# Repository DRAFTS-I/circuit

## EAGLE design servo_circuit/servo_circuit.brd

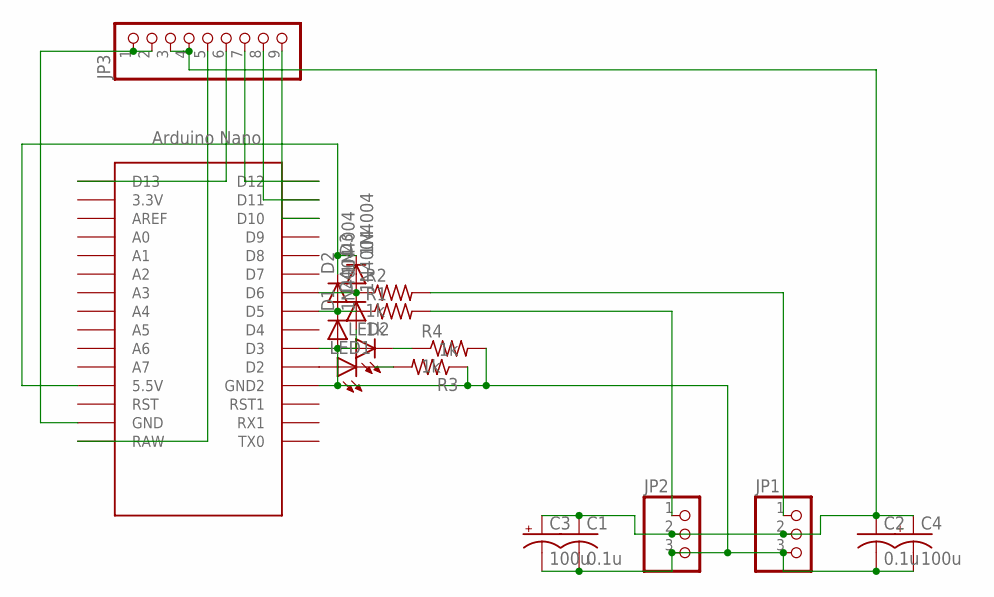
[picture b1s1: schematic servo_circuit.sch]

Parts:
C1, C2: 0.1u; C050-024X044
C3, C4: 100u; TT2D5
D1, D2, D3, D4: 1N4004; DO41-10
JP1, JP2: PINHD-1X3; 1X03
JP3: PINHD-1X9; 1X09
LED1, LED2: LED3MM
R1, R2, R3, R4: 1k; 0309V
U$1: NANO

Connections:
unnamed: LED1.A, U$1.D2
unnamed: JP3.1, JP3.2, U$1.GND
unnamed: C1.1, C2.1, C3.+, C4.+, JP1.2, JP2.2, JP3.3, JP3.4
unnamed: LED2.A, U$1.D3
unnamed: JP2.1, R1.2
unnamed: JP1.1, R2.2
unnamed: D1.C, D2.A, R1.1, U$1.D5
unnamed: D3.A, D4.C, R2.1, U$1.D6
unnamed: D2.C, D3.C, U$1.5V (5.5V)
unnamed: C1.2, C2.2, C3.-, C4.-, D1.A, D4.A, JP1.3, JP2.3, R3.1, R4.2, U$1.GND1 (GND2)
unnamed: LED2.K (C), R4.1
unnamed: JP3.5, U$1.RAW
unnamed: JP3.6, U$1.D13
unnamed: JP3.7, U$1.D12
unnamed: JP3.8, U$1.D11
unnamed: JP3.9, U$1.D10
unnamed: LED1.K (C), R3.2

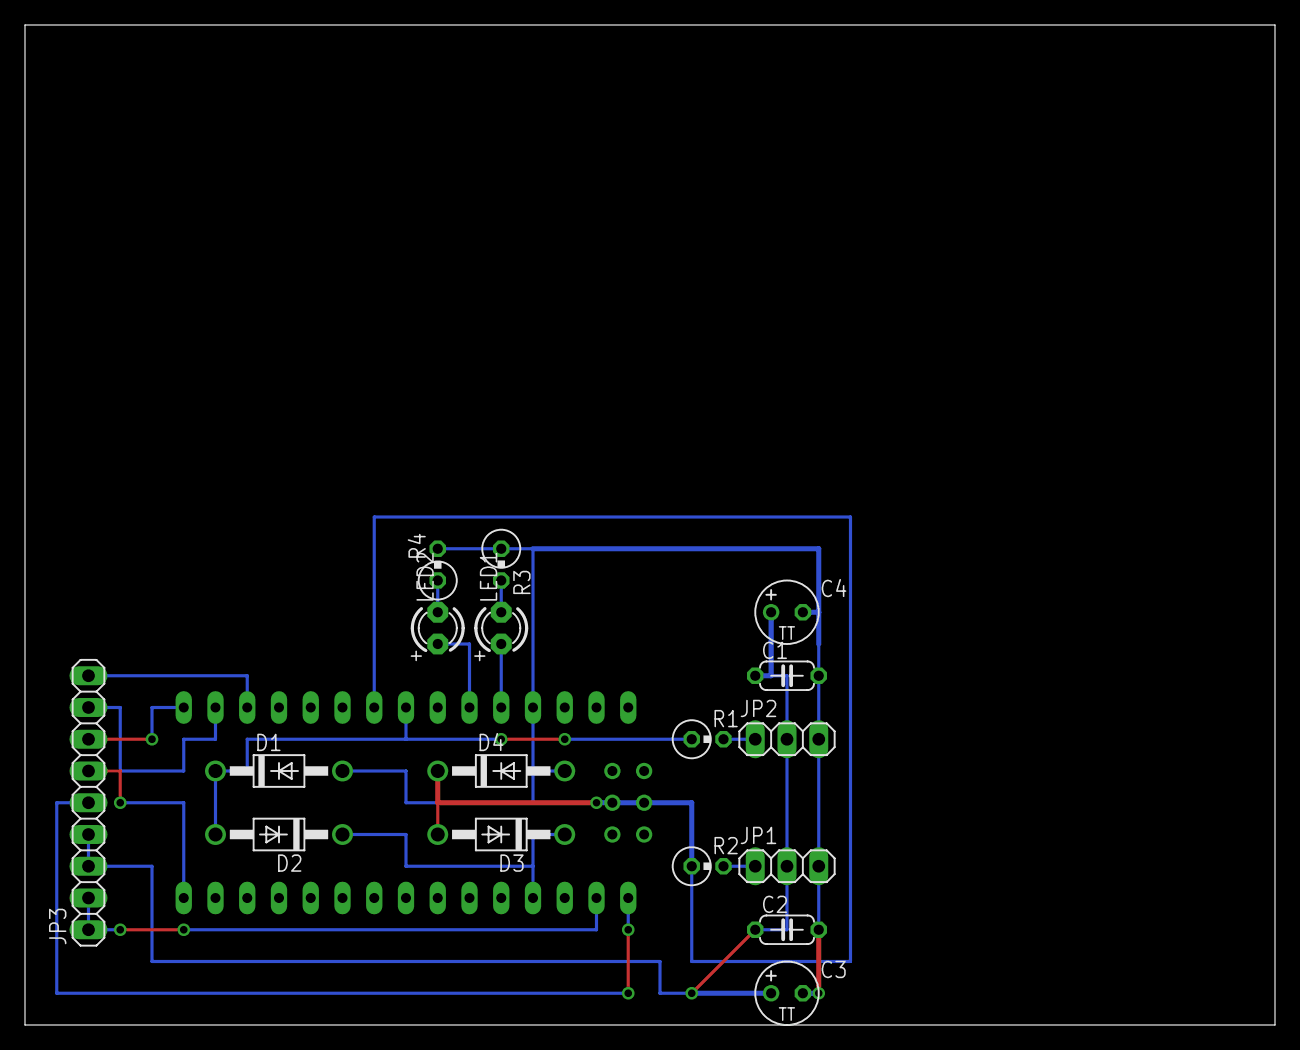
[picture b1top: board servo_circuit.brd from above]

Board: 2 copper layers, 100.0 x 80.0 mm, 18 parts (0 on the bottom side), 17 nets.

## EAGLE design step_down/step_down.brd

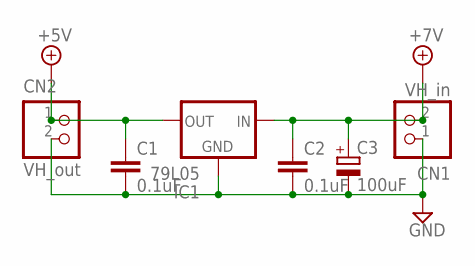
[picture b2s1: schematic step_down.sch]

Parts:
C1, C2: 0.1uF; C050-025X075
C3: 100uF; E2-5
CN1: VH_in; B2P-VH
CN2: VH_out; B2P-VH
IC1: 79L05; 79LXX

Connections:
+5V: C1.1, CN2.1, IC1.OUT
+7V: C2.1, C3.+, CN1.2, IC1.IN
GND: C1.2, C2.2, C3.-, CN1.1, CN2.2, IC1.GND

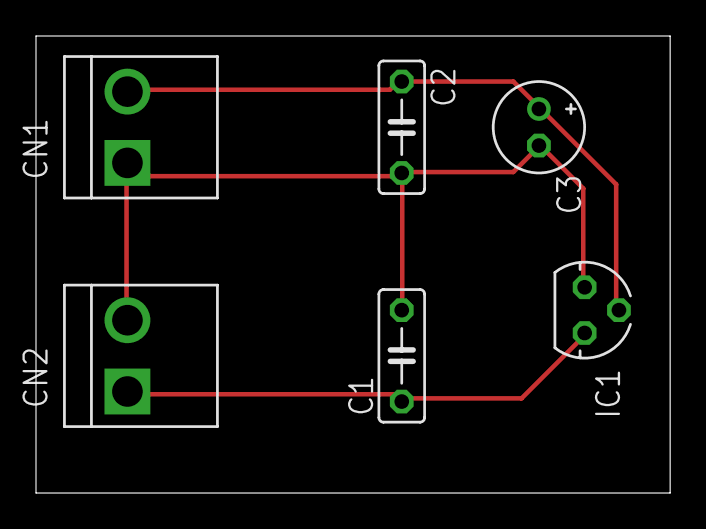
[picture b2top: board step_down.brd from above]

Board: 2 copper layers, 35.2 x 25.4 mm, 6 parts (0 on the bottom side), 3 nets.

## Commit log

2017-08-11 [add]new file
2017-08-13 [save]finished_servo
